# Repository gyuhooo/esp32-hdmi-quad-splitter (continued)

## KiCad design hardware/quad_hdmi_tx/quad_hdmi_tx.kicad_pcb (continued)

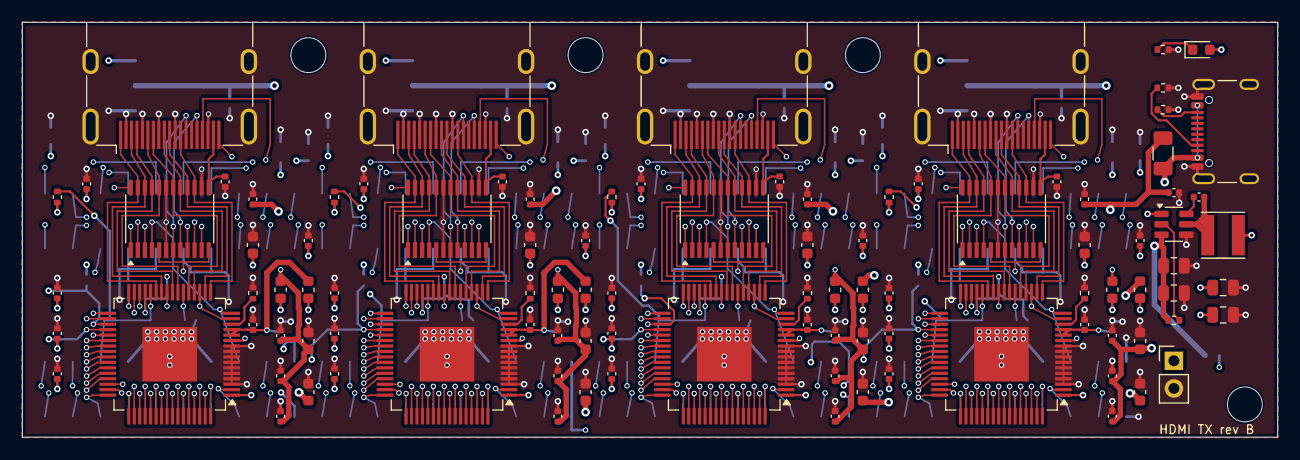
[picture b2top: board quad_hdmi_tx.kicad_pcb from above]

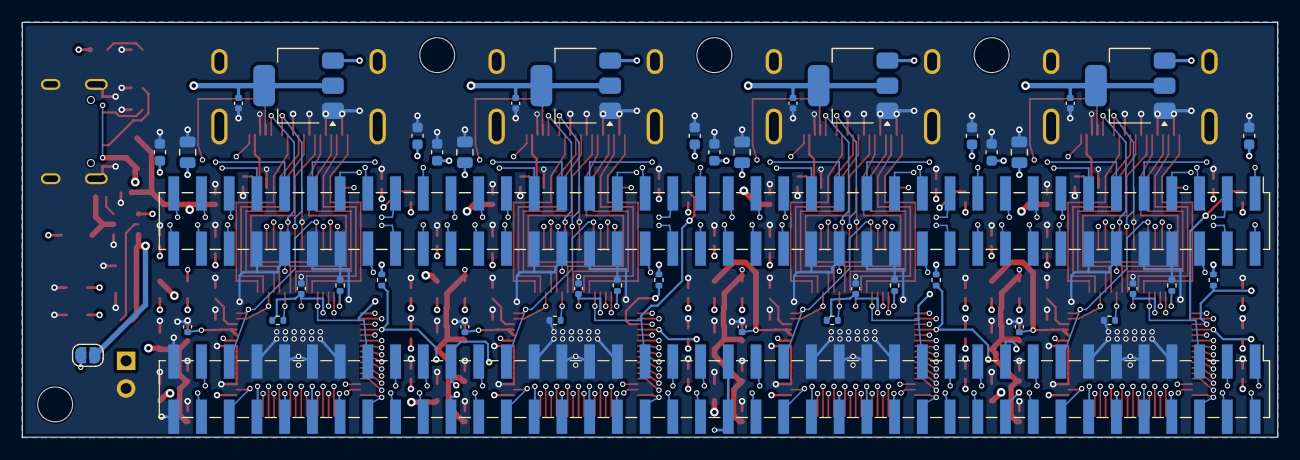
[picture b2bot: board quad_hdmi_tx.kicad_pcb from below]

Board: 6 copper layers, 115.0 x 38.0 mm, 147 parts (43 on the bottom side), 223 nets.

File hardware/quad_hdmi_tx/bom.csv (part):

Reference,Value,Footprint,MPN,Description
C51,0.1uF,Capacitor_SMD:C_0402_1005Metric,GRM155R71C104KA88D,0.1uF 16V X7R 0402 (bootstrap)
C52,10uF,Capacitor_SMD:C_0805_2012Metric,GRM21BR61A106KE19L,10uF 10V X5R 0805
C53,10uF,Capacitor_SMD:C_0805_2012Metric,GRM21BR61A106KE19L,10uF 10V X5R 0805
C54,0.1uF,Capacitor_SMD:C_0402_1005Metric,GRM155R71C104KA88D,0.1uF 16V X7R 0402
C55,22uF,Capacitor_SMD:C_0805_2012Metric,GRM21BR60J226ME39L,22uF 6.3V X5R 0805
C56,22uF,Capacitor_SMD:C_0805_2012Metric,GRM21BR60J226ME39L,22uF 6.3V X5R 0805
C101,10uF,Capacitor_SMD:C_0603_1608Metric,GRM188R60J106ME47D,10uF 6.3V X5R 0603
C102,22uF,Capacitor_SMD:C_0805_2012Metric,GRM21BR60J226ME39L,22uF 6.3V X5R 0805
C103,0.1uF,Capacitor_SMD:C_0402_1005Metric,GRM155R71C104KA88D,0.1uF 16V X7R 0402
C104,0.1uF,Capacitor_SMD:C_0402_1005Metric,GRM155R71C104KA88D,0.1uF 16V X7R 0402
C105,0.1uF,Capacitor_SMD:C_0402_1005Metric,GRM155R71C104KA88D,0.1uF 16V X7R 0402
C106,0.1uF,Capacitor_SMD:C_0402_1005Metric,GRM155R71C104KA88D,0.1uF 16V X7R 0402
C107,0.1uF,Capacitor_SMD:C_0402_1005Metric,GRM155R71C104KA88D,0.1uF 16V X7R 0402
C108,10uF,Capacitor_SMD:C_0603_1608Metric,GRM188R60J106ME47D,10uF 6.3V X5R 0603
C109,0.1uF,Capacitor_SMD:C_0402_1005Metric,GRM155R71C104KA88D,0.1uF 16V X7R 0402
C110,0.1uF,Capacitor_SMD:C_0402_1005Metric,GRM155R71C104KA88D,0.1uF 16V X7R 0402
C111,0.1uF,Capacitor_SMD:C_0402_1005Metric,GRM155R71C104KA88D,0.1uF 16V X7R 0402
C112,10uF,Capacitor_SMD:C_0603_1608Metric,GRM188R60J106ME47D,10uF 6.3V X5R 0603
C113,0.1uF,Capacitor_SMD:C_0402_1005Metric,GRM155R71C104KA88D,0.1uF 16V X7R 0402
C114,0.1uF,Capacitor_SMD:C_0402_1005Metric,GRM155R71C104KA88D,0.1uF 16V X7R 0402
C115,1uF,Capacitor_SMD:C_0603_1608Metric,GRM188R61A105KA61D,1uF 10V X5R 0603
C116,0.1uF,Capacitor_SMD:C_0402_1005Metric,GRM155R71C104KA88D,0.1uF 16V X7R 0402
C117,0.1uF,Capacitor_SMD:C_0402_1005Metric,GRM155R71C104KA88D,0.1uF 16V X7R 0402
C118,1uF,Capacitor_SMD:C_0603_1608Metric,GRM188R61A105KA61D,1uF 10V X5R 0603
C119,0.1uF,Capacitor_SMD:C_0402_1005Metric,GRM155R71C104KA88D,0.1uF 16V X7R 0402
C120,0.1uF,Capacitor_SMD:C_0402_1005Metric,GRM155R71C104KA88D,0.1uF 16V X7R 0402
C201,10uF,Capacitor_SMD:C_0603_1608Metric,GRM188R60J106ME47D,10uF 6.3V X5R 0603
C202,22uF,Capacitor_SMD:C_0805_2012Metric,GRM21BR60J226ME39L,22uF 6.3V X5R 0805
C203,0.1uF,Capacitor_SMD:C_0402_1005Metric,GRM155R71C104KA88D,0.1uF 16V X7R 0402
C204,0.1uF,Capacitor_SMD:C_0402_1005Metric,GRM155R71C104KA88D,0.1uF 16V X7R 0402
C205,0.1uF,Capacitor_SMD:C_0402_1005Metric,GRM155R71C104KA88D,0.1uF 16V X7R 0402
C206,0.1uF,Capacitor_SMD:C_0402_1005Metric,GRM155R71C104KA88D,0.1uF 16V X7R 0402
C207,0.1uF,Capacitor_SMD:C_0402_1005Metric,GRM155R71C104KA88D,0.1uF 16V X7R 0402
C208,10uF,Capacitor_SMD:C_0603_1608Metric,GRM188R60J106ME47D,10uF 6.3V X5R 0603
C209,0.1uF,Capacitor_SMD:C_0402_1005Metric,GRM155R71C104KA88D,0.1uF 16V X7R 0402
C210,0.1uF,Capacitor_SMD:C_0402_1005Metric,GRM155R71C104KA88D,0.1uF 16V X7R 0402
C211,0.1uF,Capacitor_SMD:C_0402_1005Metric,GRM155R71C104KA88D,0.1uF 16V X7R 0402
C212,10uF,Capacitor_SMD:C_0603_1608Metric,GRM188R60J106ME47D,10uF 6.3V X5R 0603
C213,0.1uF,Capacitor_SMD:C_0402_1005Metric,GRM155R71C104KA88D,0.1uF 16V X7R 0402
C214,0.1uF,Capacitor_SMD:C_0402_1005Metric,GRM155R71C104KA88D,0.1uF 16V X7R 0402
C215,1uF,Capacitor_SMD:C_0603_1608Metric,GRM188R61A105KA61D,1uF 10V X5R 0603
C216,0.1uF,Capacitor_SMD:C_0402_1005Metric,GRM155R71C104KA88D,0.1uF 16V X7R 0402
C217,0.1uF,Capacitor_SMD:C_0402_1005Metric,GRM155R71C104KA88D,0.1uF 16V X7R 0402
C218,1uF,Capacitor_SMD:C_0603_1608Metric,GRM188R61A105KA61D,1uF 10V X5R 0603
C219,0.1uF,Capacitor_SMD:C_0402_1005Metric,GRM155R71C104KA88D,0.1uF 16V X7R 0402
C220,0.1uF,Capacitor_SMD:C_0402_1005Metric,GRM155R71C104KA88D,0.1uF 16V X7R 0402
C301,10uF,Capacitor_SMD:C_0603_1608Metric,GRM188R60J106ME47D,10uF 6.3V X5R 0603
C302,22uF,Capacitor_SMD:C_0805_2012Metric,GRM21BR60J226ME39L,22uF 6.3V X5R 0805
C303,0.1uF,Capacitor_SMD:C_0402_1005Metric,GRM155R71C104KA88D,0.1uF 16V X7R 0402
C304,0.1uF,Capacitor_SMD:C_0402_1005Metric,GRM155R71C104KA88D,0.1uF 16V X7R 0402
C305,0.1uF,Capacitor_SMD:C_0402_1005Metric,GRM155R71C104KA88D,0.1uF 16V X7R 0402
C306,0.1uF,Capacitor_SMD:C_0402_1005Metric,GRM155R71C104KA88D,0.1uF 16V X7R 0402
C307,0.1uF,Capacitor_SMD:C_0402_1005Metric,GRM155R71C104KA88D,0.1uF 16V X7R 0402
C308,10uF,Capacitor_SMD:C_0603_1608Metric,GRM188R60J106ME47D,10uF 6.3V X5R 0603
C309,0.1uF,Capacitor_SMD:C_0402_1005Metric,GRM155R71C104KA88D,0.1uF 16V X7R 0402
C310,0.1uF,Capacitor_SMD:C_0402_1005Metric,GRM155R71C104KA88D,0.1uF 16V X7R 0402
C311,0.1uF,Capacitor_SMD:C_0402_1005Metric,GRM155R71C104KA88D,0.1uF 16V X7R 0402
C312,10uF,Capacitor_SMD:C_0603_1608Metric,GRM188R60J106ME47D,10uF 6.3V X5R 0603
C313,0.1uF,Capacitor_SMD:C_0402_1005Metric,GRM155R71C104KA88D,0.1uF 16V X7R 0402
C314,0.1uF,Capacitor_SMD:C_0402_1005Metric,GRM155R71C104KA88D,0.1uF 16V X7R 0402
C315,1uF,Capacitor_SMD:C_0603_1608Metric,GRM188R61A105KA61D,1uF 10V X5R 0603
C316,0.1uF,Capacitor_SMD:C_0402_1005Metric,GRM155R71C104KA88D,0.1uF 16V X7R 0402
C317,0.1uF,Capacitor_SMD:C_0402_1005Metric,GRM155R71C104KA88D,0.1uF 16V X7R 0402
C318,1uF,Capacitor_SMD:C_0603_1608Metric,GRM188R61A105KA61D,1uF 10V X5R 0603
C319,0.1uF,Capacitor_SMD:C_0402_1005Metric,GRM155R71C104KA88D,0.1uF 16V X7R 0402
C320,0.1uF,Capacitor_SMD:C_0402_1005Metric,GRM155R71C104KA88D,0.1uF 16V X7R 0402
C401,10uF,Capacitor_SMD:C_0603_1608Metric,GRM188R60J106ME47D,10uF 6.3V X5R 0603
C402,22uF,Capacitor_SMD:C_0805_2012Metric,GRM21BR60J226ME39L,22uF 6.3V X5R 0805
C403,0.1uF,Capacitor_SMD:C_0402_1005Metric,GRM155R71C104KA88D,0.1uF 16V X7R 0402
C404,0.1uF,Capacitor_SMD:C_0402_1005Metric,GRM155R71C104KA88D,0.1uF 16V X7R 0402
C405,0.1uF,Capacitor_SMD:C_0402_1005Metric,GRM155R71C104KA88D,0.1uF 16V X7R 0402
C406,0.1uF,Capacitor_SMD:C_0402_1005Metric,GRM155R71C104KA88D,0.1uF 16V X7R 0402
C407,0.1uF,Capacitor_SMD:C_0402_1005Metric,GRM155R71C104KA88D,0.1uF 16V X7R 0402
C408,10uF,Capacitor_SMD:C_0603_1608Metric,GRM188R60J106ME47D,10uF 6.3V X5R 0603
C409,0.1uF,Capacitor_SMD:C_0402_1005Metric,GRM155R71C104KA88D,0.1uF 16V X7R 0402
C410,0.1uF,Capacitor_SMD:C_0402_1005Metric,GRM155R71C104KA88D,0.1uF 16V X7R 0402
C411,0.1uF,Capacitor_SMD:C_0402_1005Metric,GRM155R71C104KA88D,0.1uF 16V X7R 0402
C412,10uF,Capacitor_SMD:C_0603_1608Metric,GRM188R60J106ME47D,10uF 6.3V X5R 0603
C413,0.1uF,Capacitor_SMD:C_0402_1005Metric,GRM155R71C104KA88D,0.1uF 16V X7R 0402
C414,0.1uF,Capacitor_SMD:C_0402_1005Metric,GRM155R71C104KA88D,0.1uF 16V X7R 0402
C415,1uF,Capacitor_SMD:C_0603_1608Metric,GRM188R61A105KA61D,1uF 10V X5R 0603
C416,0.1uF,Capacitor_SMD:C_0402_1005Metric,GRM155R71C104KA88D,0.1uF 16V X7R 0402
C417,0.1uF,Capacitor_SMD:C_0402_1005Metric,GRM155R71C104KA88D,0.1uF 16V X7R 0402
C418,1uF,Capacitor_SMD:C_0603_1608Metric,GRM188R61A105KA61D,1uF 10V X5R 0603
C419,0.1uF,Capacitor_SMD:C_0402_1005Metric,GRM155R71C104KA88D,0.1uF 16V X7R 0402
C420,0.1uF,Capacitor_SMD:C_0402_1005Metric,GRM155R71C104KA88D,0.1uF 16V X7R 0402
D1,PWR,LED_SMD:LED_0603_1608Metric,LTST-C193KGKT-5A,Green LED 0603
F1,2A,Fuse:Fuse_1206_3216Metric,1206L200/12SLYR,"PTC resettable fuse 2 A hold, 1206"
FB11,120R@100MHz,Inductor_SMD:L_0603_1608Metric,BLM18PG121SN1D,Ferrite bead 0603
FB12,120R@100MHz,Inductor_SMD:L_0603_1608Metric,BLM18PG121SN1D,Ferrite bead 0603
FB21,120R@100MHz,Inductor_SMD:L_0603_1608Metric,BLM18PG121SN1D,Ferrite bead 0603
FB22,120R@100MHz,Inductor_SMD:L_0603_1608Metric,BLM18PG121SN1D,Ferrite bead 0603
FB31,120R@100MHz,Inductor_SMD:L_0603_1608Metric,BLM18PG121SN1D,Ferrite bead 0603
FB32,120R@100MHz,Inductor_SMD:L_0603_1608Metric,BLM18PG121SN1D,Ferrite bead 0603
FB41,120R@100MHz,Inductor_SMD:L_0603_1608Metric,BLM18PG121SN1D,Ferrite bead 0603
FB42,120R@100MHz,Inductor_SMD:L_0603_1608Metric,BLM18PG121SN1D,Ferrite bead 0603
H1,M3,MountingHole:MountingHole_3.2mm,,Mounting hole M3
H2,M3,MountingHole:MountingHole_3.2mm,,Mounting hole M3
H3,M3,MountingHole:MountingHole_3.2mm,,Mounting hole M3
H4,M3,MountingHole:MountingHole_3.2mm,,Mounting hole M3
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
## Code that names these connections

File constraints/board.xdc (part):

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set_property BITSTREAM.GENERAL.COMPRESS TRUE [current_design]

## 100 MHz oscillator (X1 -> MRCC) and reset button
set_property -dict {PACKAGE_PIN D4 IOSTANDARD LVCMOS33} [get_ports {clk100}]
set_property -dict {PACKAGE_PIN T3 IOSTANDARD LVCMOS33 PULLUP true} [get_ports {rst_n}]
create_clock -period 10.000 -name clk100 [get_ports clk100]

## ADV7513 parallel RGB (carrier J1/J2), I2C, LEDs
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set_property -dict {PACKAGE_PIN R12 IOSTANDARD LVCMOS33} [get_ports {led[3]}]

## Spare I/O on the main board (not used by hdl/top.v - uncomment and add the ports to use them). SW0-3: DIP switch to GND, enable PULLUP.
# set_property -dict {PACKAGE_PIN E5 IOSTANDARD LVCMOS33} [get_ports {pmod_1}]
# set_property -dict {PACKAGE_PIN E6 IOSTANDARD LVCMOS33} [get_ports {pmod_2}]
# set_property -dict {PACKAGE_PIN F5 IOSTANDARD LVCMOS33} [get_ports {pmod_3}]
# set_property -dict {PACKAGE_PIN G5 IOSTANDARD LVCMOS33} [get_ports {pmod_4}]
# set_property -dict {PACKAGE_PIN H5 IOSTANDARD LVCMOS33} [get_ports {pmod_7}]
# set_property -dict {PACKAGE_PIN J5 IOSTANDARD LVCMOS33} [get_ports {pmod_8}]
# set_property -dict {PACKAGE_PIN K5 IOSTANDARD LVCMOS33} [get_ports {pmod_9}]
# set_property -dict {PACKAGE_PIN L5 IOSTANDARD LVCMOS33} [get_ports {pmod_10}]
# set_property -dict {PACKAGE_PIN T13 IOSTANDARD LVCMOS33 PULLUP true} [get_ports {sw0}]
# set_property -dict {PACKAGE_PIN R13 IOSTANDARD LVCMOS33 PULLUP true} [get_ports {sw1}]
# set_property -dict {PACKAGE_PIN T14 IOSTANDARD LVCMOS33 PULLUP true} [get_ports {sw2}]
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
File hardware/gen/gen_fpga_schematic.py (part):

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    res(sh, "4.7k", 325, 80, "+3V3", "TDI", "4.7k 0402 (TDI pull-up)", role="r_tdi")
    # PROGRAM_B ボタン
    b = sh.symbol("Switch:SW_Push", "SW1", "PROG", (265, 110), "Button_Switch_SMD:SW_Push_1P1T_NO_CK_KMR2", "KMR221GLFS", "Tactile switch 4.2x2.8 mm (reconfigure)", rot=0)
    x, y, _, _, _ = b["1"]; sh.wire(x, y, x - 5.08, y); sh.label("PROGRAM_B", x - 5.08, y, 180)
    x, y, _, _, _ = b["2"]; sh.wire(x, y, x + 2.54, y); sh.wire(x + 2.54, y, x + 2.54, y + 2.54); sh.power("GND", x + 2.54, y + 2.54, down=True)
    # DONE LED (緑): DONE -> 1k -> LED -> GND
    res(sh, "1k", 295, 110, "DONE", "DONE_LED", "1k 0402 (DONE LED)", role="r_done_led")
    d = sh.symbol("Device:LED", "D2", "DONE", (295, 135), "LED_SMD:LED_0603_1608Metric", LED_G, "Green LED 0603 (DONE)")
    sh.label_pin(d, "2", "DONE_LED"); sh.label_pin(d, "1", "GND")
    # INIT LED (赤): +3V3 -> 1k -> LED -> INIT_B (INIT_B が Low のとき点灯)
    res(sh, "1k", 280, 110, "+3V3", "INIT_LED", "1k 0402 (INIT LED)", role="r_init_led")
    d = sh.symbol("Device:LED", "D3", "INIT", (280, 135), "LED_SMD:LED_0603_1608Metric", LED_R, "Red LED 0603 (INIT_B low)")
    sh.label_pin(d, "2", "INIT_LED"); sh.label_pin(d, "1", "INIT_B")
    # ---- QSPI フラッシュ
    f = sh.symbol("Memory_Flash:W25Q32JVSS", "U2", "W25Q32JVSSIQ", (330, 200), None, "W25Q32JVSSIQ", "32 Mbit QSPI flash, SOIC-8 208 mil (configuration memory)")
    for num, net in (("1", "QSPI_CS"), ("2", "QSPI_D1"), ("3", "QSPI_D2"), ("5", "QSPI_D0"), ("6", "CCLK"), ("7", "QSPI_D3")):
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    res(sh, "4.7k", 250, 230, "+3V3", "QSPI_CS", "4.7k 0402 (flash CS pull-up)", role="r_cs")
    res(sh, "4.7k", 265, 230, "+3V3", "QSPI_D2", "4.7k 0402 (flash WP pull-up)", role="r_wp")
    res(sh, "4.7k", 280, 230, "+3V3", "QSPI_D3", "4.7k 0402 (flash HOLD pull-up)", role="r_hold")
    sh.text("Flash: W25Q32JV (32 Mbit >= 17.5 Mbit bitstream). Vivado: BITSTREAM.CONFIG.SPI_BUSWIDTH 4, CONFIGRATE 33. CCLK/D0-D3/CS are the bank-14 dual-purpose pins.", 230, 250, 1.5)
    # ---- JTAG ヘッダ
    j3 = sh.symbol("Connector_Generic:Conn_02x07_Odd_Even", "J3", "JTAG 2x7", (60, 230), "Connector_PinHeader_2.00mm:PinHeader_2x07_P2.00mm_Vertical",
                   "", "2x7 pin header 2.0 mm (Xilinx 14-pin JTAG cable: 2 VREF, 4 TMS, 6 TCK, 8 TDO, 10 TDI, odd = GND)")
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        sh.label_pin(j4, num, net)
    # ---- 発振器 100 MHz
    xo = sh.symbol("Oscillator:ASE-xxxMHz", "X1", "100MHz", (180, 230), None, "ASEM1-100.000MHZ-LC-T", "100 MHz 3.3 V MEMS oscillator, 3.2x2.5 mm (LVCMOS, +/-50 ppm)")
    sh.label_pin(xo, "3", "CLK100")
    x, y, _, _, _ = xo["1"]; sh.wire(x, y, x - 5.08, y); sh.power("+3V3", x - 5.08, y)
    x, y, _, _, _ = xo["4"]; sh.power("+3V3", x, y)
    x, y, _, _, _ = xo["2"]; sh.power("GND", x, y, down=True)
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def carrier_sheet(sheet_uuid, page):
    sh = Sheet("carrier_if.kicad_sch", "Carrier board sockets J1/J2 (mate quad_hdmi_tx J7/J8)", sheet_uuid, page)
    sh.text("J1/J2: 2x40 female sockets (2.54 mm, THT) at the mirror positions of the carrier's bottom-side headers J7/J8. Pin n of J1 = carrier J7 pin n, J2 = J8.", 20, 20, 2.0)
    sh.text("124 signals (3.3 V LVCMOS, up to 148.5 MHz SDR), 34 GND, FPGA_5V on J2 pins 39/40 (optional 5 V link between the boards, JP1 here and JP1 on the carrier).", 20, 26, 1.5)
    nets = {(h, p): s for h, p, s, x, y in F.HEADER_ALL}
    for ref, x in (("J1", 110), ("J2", 300)):
        j = sh.symbol("Connector_Generic:Conn_02x40_Odd_Even", ref, "CARRIER_" + ref, (x, 150),
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        for p in range(1, 81):
            sh.net_or_power(j, str(p), nets[(ref, p)])
    jp = sh.symbol("Jumper:SolderJumper_2_Open", "JP1", "5V<->CARRIER", (200, 250), "Jumper:SolderJumper-2_P1.3mm_Open_RoundedPad1.0x1.5mm",
                   "", "Solder jumper: link +5V with FPGA_5V (J2 pins 39/40)")
    x, y, _, _, _ = jp["1"]; sh.wire(x, y, x - 5.08, y); sh.power("+5V", x - 5.08, y)
    x, y, _, _, _ = jp["2"]; sh.wire(x, y, x + 5.08, y); sh.label("FPGA_5V", x + 5.08, y, 0)
    sh.text("JP1 open (default): each board has its own USB-C supply. Close JP1 on both boards to power the pair from one USB-C (max 2 A total).", 20, 262, 1.5)
    sh.write()
    return sh
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    sh.text("SW0-3: closed = low. Enable PULLUP in the XDC. Not used by the current HDL (reserved for video-mode selection).", 150, 125, 1.5)
    # リセットボタン
    b = sh.symbol("Switch:SW_Push", "SW2", "RST", (250, 95), "Button_Switch_SMD:SW_Push_1P1T_NO_CK_KMR2", "KMR221GLFS", "Tactile switch 4.2x2.8 mm (reset)")
    x, y, _, _, _ = b["1"]; sh.wire(x, y, x - 5.08, y); sh.label("RST_N", x - 5.08, y, 180)
    x, y, _, _, _ = b["2"]; sh.wire(x, y, x + 2.54, y); sh.wire(x + 2.54, y, x + 2.54, y + 2.54); sh.power("GND", x + 2.54, y + 2.54, down=True)
    res(sh, "10k", 270, 80, "+3V3", "RST_N", "10k 0402 (reset pull-up)", role="r_rst")
    cap(sh, "0.1uF", 285, 80, "RST_N", "GND", role="c_rst")
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    px, py, _, _, _ = u["2"]; sh.wire(px, py, px - 5.08, py); sh.label(en_net, px - 5.08, py, 180)
    px, py, _, _, _ = u["4"]; sh.power("GND", px, py, down=True)
    px, py, _, _, _ = u["5"]; sh.wire(px, py, px + 7.62, py); sh.label(f"{ref_u}_SW", px + 7.62, py, 0)
    px, py, _, _, _ = u["6"]; sh.wire(px, py, px + 7.62, py); sh.label(f"{ref_u}_BST", px + 7.62, py, 0)
    px, py, _, _, _ = u["1"]
    if fb_div:
        sh.wire(px, py, px - 5.08, py); sh.label(f"{ref_u}_FB", px - 5.08, py, 180)
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    sh.text("Vout = 0.8 V x (1 + Rtop/Rbot): U3 10k/40.2k = 1.00 V, U4 24.9k/20k = 1.80 V. L 4.7uH, CIN 2x10uF, COUT 2x22uF (+ FPGA bulk caps on fpga_cfg sheet).", 160, 262, 1.5)
    # 電源 LED
    d = sh.symbol("Device:LED", "D1", "PWR", (60, 200), "LED_SMD:LED_0603_1608Metric", LED_G, "Green LED 0603 (3.3 V power)")
    sh.label_pin(d, "2", "PWR_LED"); sh.label_pin(d, "1", "GND")
    res(sh, "1k", 60, 170, "+3V3", "PWR_LED", "1k 0402 (power LED)", role="r_pwr_led")
    # GND フラグ
    sh.pwr_flag(100, 200); sh.wire(100, 200, 100, 205); sh.power("GND", 100, 205, down=True)
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
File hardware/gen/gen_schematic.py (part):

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    jp = sh.symbol("Jumper:SolderJumper_2_Open", "JP1", "5V->FPGA", (130, 250), "Jumper:SolderJumper-2_P1.3mm_Open_RoundedPad1.0x1.5mm",
                   "", "Solder jumper: feed +5V to FPGA board via J8 pins 39/40")
    x, y, _, _, _ = jp["1"]; sh.wire(x, y, x - 5.08, y); sh.power("+5V", x - 5.08, y)
    x, y, _, _, _ = jp["2"]; sh.wire(x, y, x + 5.08, y); sh.label("FPGA_5V", x + 5.08, y, 0)
    sh.text("JP1 closed: this board powers the FPGA board through J8 pins 39-40 (FPGA_5V). Leave open if the FPGA board has its own supply.", 20, 262, 1.5)
    sh.write()
    return sh

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    # バック
    u = sh.symbol("Regulator_Switching:AP63203WU", "U5", "AP63203WU", (230, 110), None, "AP63203WU-7", "3.3 V 2 A synchronous buck, TSOT-23-6")
    x, y, _, _, _ = u["3"]; sh.wire(x, y, x - 10.16, y); sh.power("+5V", x - 10.16, y); sh.junction(x - 10.16, y)
    x2, y2, _, _, _ = u["2"]; sh.wire(x2, y2, x2 - 5.08, y2); sh.label("BUCK_EN", x2 - 5.08, y2, 180)
    sh.two_pin("Device:R", "R7", "100k", 200, 140, "+5V", "BUCK_EN", R0402, "RC0402FR-07100KL", "100k 0402 (EN pull-up to VIN)")
    x, y, _, _, _ = u["4"]; sh.power("GND", x, y, down=True)
    x, y, _, _, _ = u["5"]; sh.wire(x, y, x + 7.62, y); sh.label("SW", x + 7.62, y, 0)
    x, y, _, _, _ = u["6"]; sh.wire(x, y, x + 7.62, y); sh.label("BST", x + 7.62, y, 0)
    x, y, _, _, _ = u["1"]; sh.wire(x, y, x + 7.62, y); sh.label("+3V3", x + 7.62, y, 0)     # 固定 3.3 V 版: FB は VOUT に直結
    sh.two_pin("Device:C", "C51", "0.1uF", 270, 140, "BST", "SW", C0402, MPN_C100N, "0.1uF 16V X7R 0402 (bootstrap)")
    # インダクタ: 横置きにするため 2 端子縦置きヘルパを使い、上=SW 下=+3V3
    sh.two_pin("Device:L", "L1", "4.7uH", 290, 140, "SW", "+3V3", "Inductor_SMD:L_Taiyo-Yuden_NR-40xx", "NR4018T4R7M", "4.7uH 2.2A shielded inductor 4x4 mm")
    sh.two_pin("Device:C", "C52", "10uF", 200, 180, "+5V", "GND", C0805, "GRM21BR61A106KE19L", "10uF 10V X5R 0805")
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    # LED
    d = sh.symbol("Device:LED", "D1", "PWR", (330, 120), "LED_SMD:LED_0603_1608Metric", "LTST-C193KGKT-5A", "Green LED 0603")
    x, y, _, _, _ = d["2"]; sh.wire(x, y, x + 5.08, y); sh.power("+3V3", x + 5.08, y)
    x, y, _, _, _ = d["1"]; sh.wire(x, y, x - 5.08, y); sh.label("LED_K", x - 5.08, y, 180)
    sh.two_pin("Device:R", "R8", "1k", 310, 140, "LED_K", "GND", R0402, "RC0402FR-071KL", "1k 0402")
    # 取付穴
    for i, x in enumerate((30, 45, 60, 75)):
        sh.symbol("Mechanical:MountingHole", f"H{i+1}", "M3", (x, 230), "MountingHole:MountingHole_3.2mm", "", "Mounting hole M3")
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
